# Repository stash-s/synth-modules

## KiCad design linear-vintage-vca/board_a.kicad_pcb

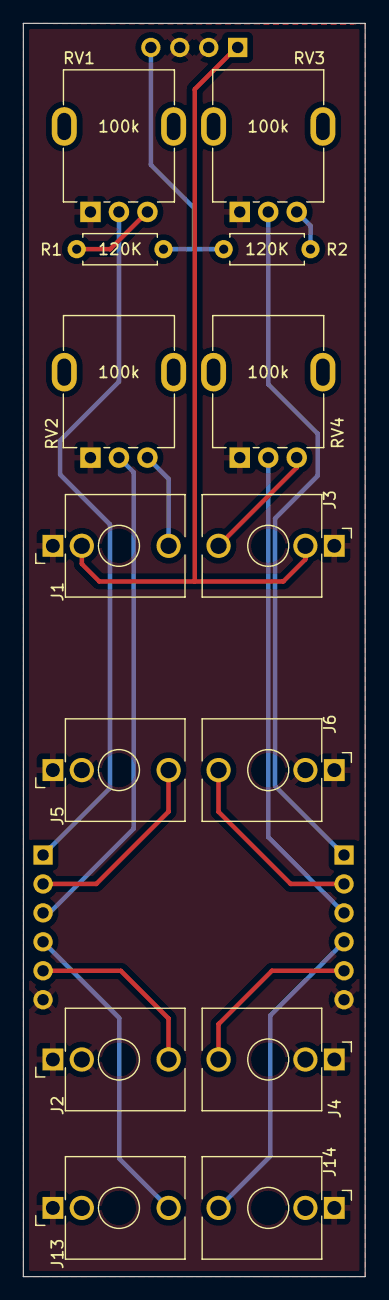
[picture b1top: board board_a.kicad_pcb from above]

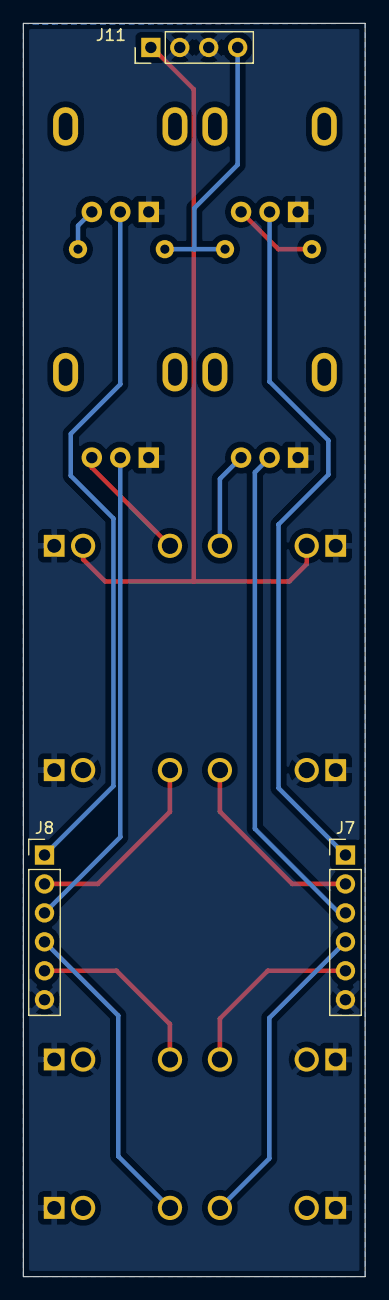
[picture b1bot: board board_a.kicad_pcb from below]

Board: 2 copper layers, 30.0 x 110.0 mm, 18 parts (3 on the bottom side), 17 nets.

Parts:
A: Board
J1, J2, J3, J4, J5, J6, J13, J14: AudioJack2; Jack_3.5mm_Switch
J7, J8: Conn_01x06_Pin; PinHeader_1x06_P2.54mm_Vertical
J11: Conn_01x04_Pin; PinHeader_1x04_P2.54mm_Vertical
R1, R2: 120K; R_Axial_DIN0207_L6.3mm_D2.5mm_P7.62mm_Horizontal
RV1, RV2, RV3, RV4: 100k; Potentiometer_Alpha_RD901F-40-00D_Single_Vertical

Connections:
+12V_A: J11.4, R1.1, R2.1
CV_A: J1.TN, J3.TN, J11.1
GND_A: J1.S, J2.S, J2.TN, J3.S, J4.S, J4.TN, J5.S, J5.TN, J6.S, J6.TN, J7.6, J8.6, J11.2, J11.3, J13.S, J14.S, RV1.1, RV2.1, RV3.1, RV4.1
unnamed: J1.T, RV2.3
unnamed: J3.T, RV4.3
unnamed: J7.1, RV1.2
unnamed: J5.T, J7.2
unnamed: J7.3, RV2.2
unnamed: J2.T, J7.5
unnamed: J8.1, RV3.2
unnamed: J6.T, J8.2
unnamed: J8.3, RV4.2
unnamed: J4.T, J8.5
unnamed: R1.2, RV1.3
unnamed: R2.2, RV3.3
OUT_1A: J7.4, J13.T
OUT_2A: J8.4, J14.T

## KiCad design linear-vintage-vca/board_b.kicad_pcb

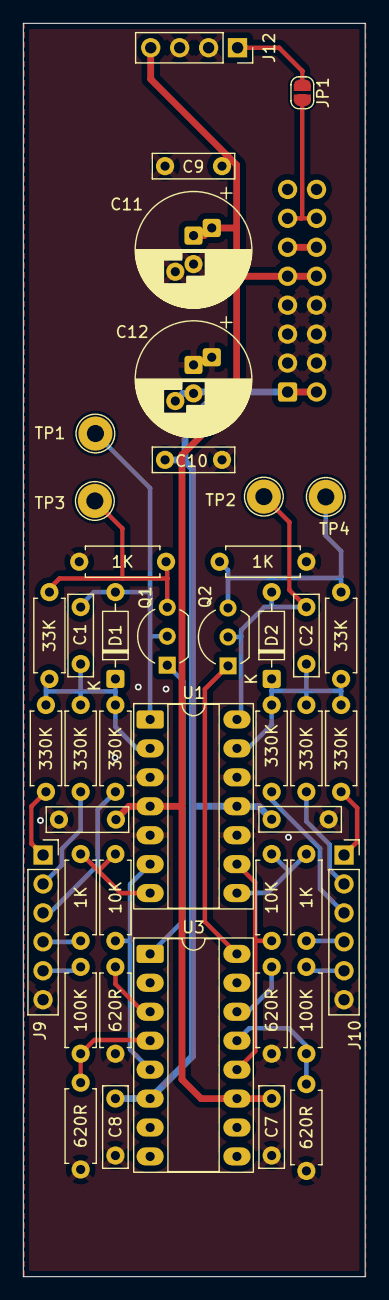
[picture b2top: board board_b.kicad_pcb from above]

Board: 2 copper layers, 30.0 x 110.0 mm, 46 parts (1 on the bottom side), 32 nets.

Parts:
B: Board
C1, C2, C5, C6, C7, C8, C9, C10: 100n; C_Rect_L7.0mm_W2.0mm_P5.00mm
C11, C12: 47uF; CP_Radial_D10.0mm_P2.50mm_P5.00mm
D1, D2: 1N4148; D_DO-35_SOD27_P7.62mm_Horizontal
J9, J10: Conn_01x10_Socket; PinSocket_1x06_P2.54mm_Vertical
J12: Conn_01x04_Socket; PinSocket_1x04_P2.54mm_Vertical
J15: Conn_02x08_Odd_Even; IDC-Header_2x08_P2.54mm_Vertical
JP1: SolderJumper_2_Open; SolderJumper-2_P1.3mm_Open_RoundedPad1.0x1.5mm
Q1, Q2: BC556; TO-92_Inline_Wide
R3, R4, R5, R6, R7, R8: 330K; R_Axial_DIN0207_L6.3mm_D2.5mm_P7.62mm_Horizontal
R9, R10: 100K; R_Axial_DIN0207_L6.3mm_D2.5mm_P7.62mm_Horizontal
R11, R12, R15, R16: 620R; R_Axial_DIN0207_L6.3mm_D2.5mm_P7.62mm_Horizontal
R13, R14: 33K; R_Axial_DIN0207_L6.3mm_D2.5mm_P7.62mm_Horizontal
R17, R18, R21, R22: 1K; R_Axial_DIN0207_L6.3mm_D2.5mm_P7.62mm_Horizontal
R19, R20: 10K; R_Axial_DIN0207_L6.3mm_D2.5mm_P7.62mm_Horizontal
TP1, TP2, TP3, TP4: TestPoint; TestPoint_Loop_D2.54mm_Drill1.5mm_Beaded
U1: TL074; DIP-14_W7.62mm_Socket_LongPads
U3: LM13700; DIP-16_W7.62mm_Socket_LongPads

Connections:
+5V: J15.11, J15.12
+12V: C5.1, C7.1, C9.1, C11.1, J12.4, J15.9, J15.10, U1.4 (V+), U3.11 (V+)
-12V: C6.2, C8.2, C10.2, C12.2, J15.1, J15.2, U1.11 (V-), U3.6 (V-)
CV_B: J15.13, J15.14, JP1.2 (B)
GND: C5.2, C6.1, C7.2, C8.1, C9.2, C10.1, C11.2, C12.1, J9.6, J10.6, J12.2, J12.3, J15.3, J15.4, J15.5, J15.6, J15.7, J15.8, R11.2, R12.2, R15.2, R16.2, R17.2, R18.2, U1.3 (+), U1.5 (+), U1.10 (+), U1.12 (+)
unnamed: C1.2, D1.2 (A), Q1.2 (B), TP1.1, U1.1
unnamed: C1.1, D1.1 (K), R3.2, R4.2, R5.2, R13.1, U1.2 (-)
unnamed: C2.2, D2.2 (A), Q2.2 (B), TP2.1, U1.14
unnamed: C2.1, D2.1 (K), R6.2, R7.2, R8.2, R14.1, U1.13 (-)
unnamed: J9.1, R3.1
unnamed: J9.2, R4.1
unnamed: J9.3, R5.1
unnamed: J9.5, R9.1
unnamed: J10.1, R6.1
unnamed: J10.2, R7.1
unnamed: J10.3, R8.1
unnamed: J10.5, R10.1
unnamed: J12.1, JP1.1 (A)
unnamed: Q1.1 (C), U3.1
unnamed: Q1.3 (E), R13.2, R17.1, TP3.1
unnamed: Q2.1 (C), U3.16
unnamed: Q2.3 (E), R14.2, R18.1, TP4.1
unnamed: R19.2, R21.1, U1.7
unnamed: R20.2, R22.1, U1.8
unnamed: R19.1, U1.6 (-), U3.5
unnamed: R20.1, U1.9 (-), U3.12
unnamed: R16.1, U3.14 (+)
unnamed: R10.2, R12.1, U3.13 (-)
unnamed: R15.1, U3.3 (+)
unnamed: R9.2, R11.1, U3.4 (-)
OUT_1B: J9.4, R21.2
OUT_2B: J10.4, R22.2
